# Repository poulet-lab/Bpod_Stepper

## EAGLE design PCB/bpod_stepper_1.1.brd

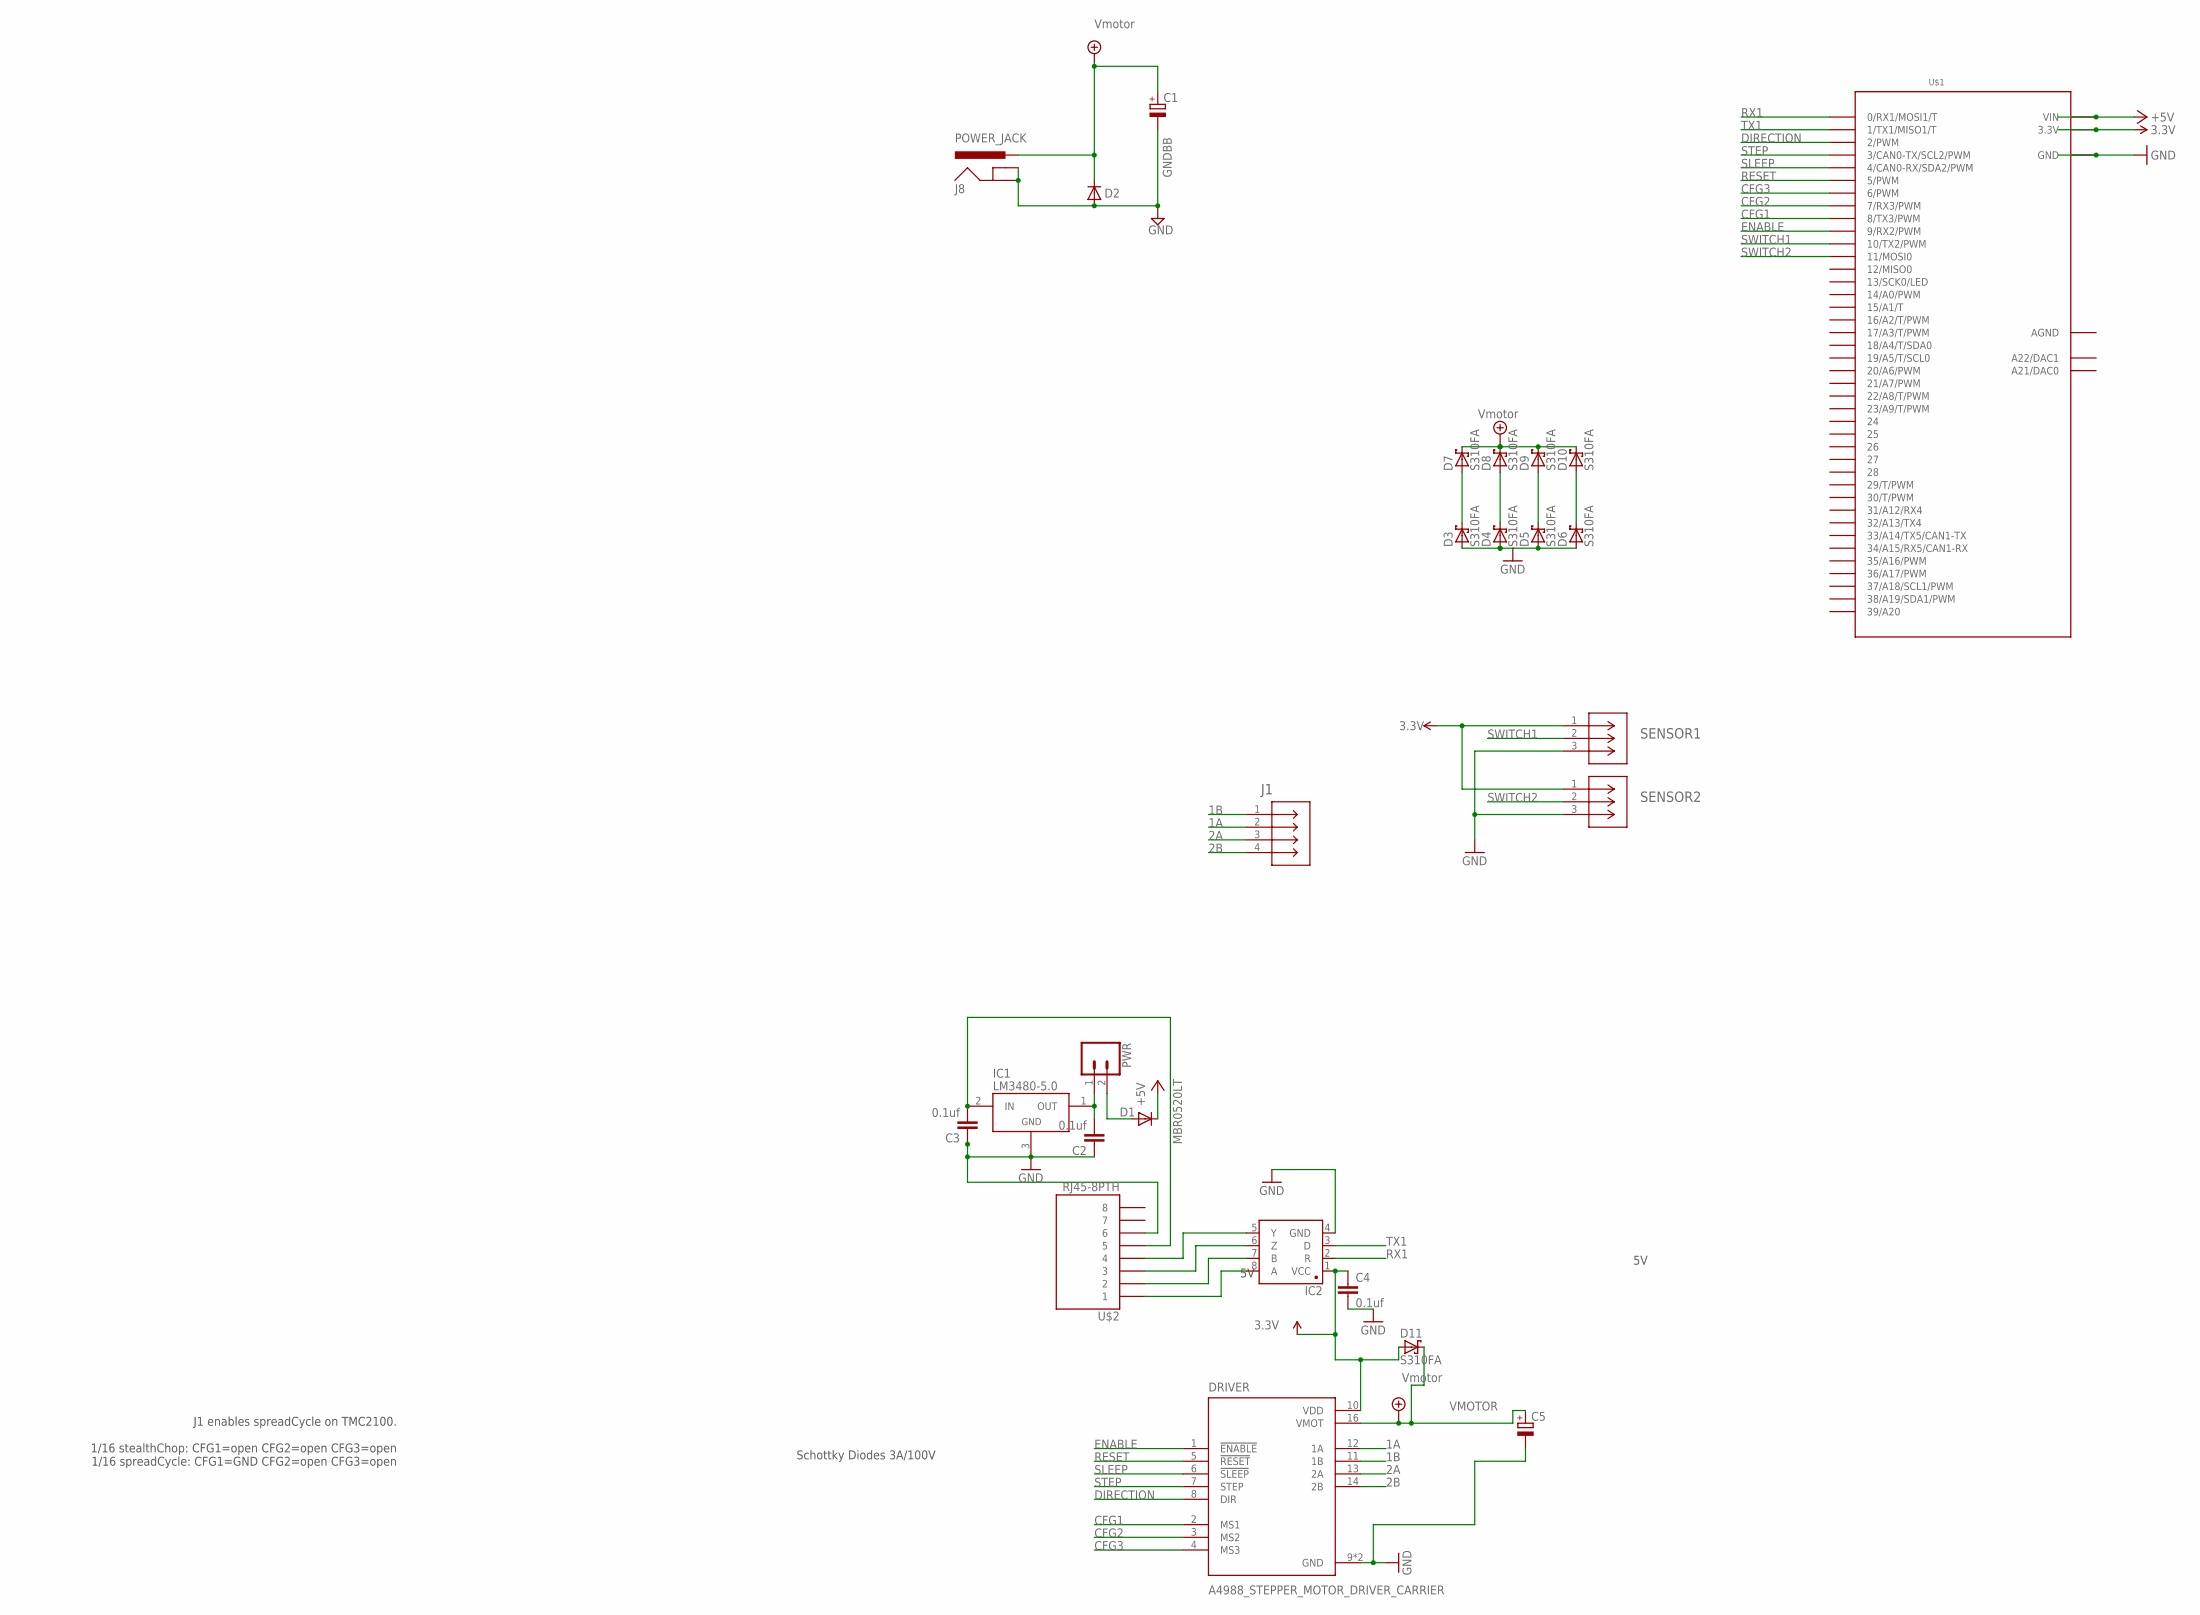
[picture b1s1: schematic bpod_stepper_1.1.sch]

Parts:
C1, C5: CPOL-EUG; PANASONIC_G
C2, C3, C4: 0.1uf; 1206@1
D1: MBR0520LT; SOD123
D2: DIODE-DO214AA; DO214AA
D3, D4, D5, D6, D7, D8, D9, D10, D11: S310FA; SOD123
DRIVER: A4988_STEPPER_MOTOR_DRIVER_CARRIER; MODULE_A4988_STEPPER_MOTOR_DRIVER_CARRIER
IC1: LM3480-5.0; SOT-23-3
IC2: SN65HVD31DR; SO08
J1: 282841-4; CONN4_282841-4_TEC
J8: POWER_JACK; POWER_JACK_PTH
PWR: CONN_02; 1X02
SENSOR1, SENSOR2: 282834-3; CONN_282834-3_TYC
U$1: TEENSY_3.6_DIL
U$2: RJ45-8PTH; RJ45-8

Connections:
1A: D4.C, D8.A, DRIVER.12 (1A), J1.2
1B: D3.C, D7.A, DRIVER.11 (1B), J1.1
2A: D5.C, D9.A, DRIVER.13 (2A), J1.3
2B: D6.C, D10.A, DRIVER.14 (2B), J1.4
3.3V: C4.1, D11.A, DRIVER.10 (VDD), IC2.1 (VCC), SENSOR1.1, SENSOR2.1, U$1.3.3V, U$1.3.3V3 (3.3V)
+5V: D1.C, U$1.VIN
AGND: U$1.AGND
CFG1: DRIVER.2 (MS1), U$1.8 (8/TX3/PWM)
CFG2: DRIVER.3 (MS2), U$1.7 (7/RX3/PWM)
CFG3: DRIVER.4 (MS3), U$1.6 (6/PWM)
DIRECTION: DRIVER.8 (DIR), U$1.2 (2/PWM)
ENABLE: DRIVER.1 (!ENABLE), U$1.9 (9/RX2/PWM)
GND: C1.-, C2.1, C3.1, C4.2, C5.-, D2.A, D3.A, D4.A, D5.A, D6.A, DRIVER.9 (GND), DRIVER.15 (GND), IC1.3 (GND), IC2.4 (GND), J8.GND, J8.GNDBREAK, SENSOR1.3, SENSOR2.3, U$1.GND, U$1.GND1 (GND), U$2.6
unnamed: IC2.8 (A), U$2.1
unnamed: IC2.7 (B), U$2.2
unnamed: IC2.6 (Z), U$2.3
unnamed: IC2.5 (Y), U$2.4
unnamed: C2.2, IC1.1 (OUT), PWR.1
unnamed: D1.A, PWR.2
unnamed: C3.2, IC1.2 (IN), U$2.5
RESET: DRIVER.5 (!RESET), U$1.5 (5/PWM)
RX1: IC2.2 (R), U$1.0 (0/RX1/MOSI1/T)
SLEEP: DRIVER.6 (!SLEEP), U$1.4 (4/CAN0-RX/SDA2/PWM)
STEP: DRIVER.7 (STEP), U$1.3 (3/CAN0-TX/SCL2/PWM)
SWITCH1: SENSOR1.2, U$1.10 (10/TX2/PWM)
SWITCH2: SENSOR2.2, U$1.11 (11/MOSI0)
TX1: IC2.3 (D), U$1.1 (1/TX1/MISO1/T)
VMOTOR: C1.+, C5.+, D2.C, D7.C, D8.C, D9.C, D10.C, D11.C, DRIVER.16 (VMOT), J8.PWR

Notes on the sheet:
GNDBB
Schottky Diodes 3A/100V
J1 enables spreadCycle on TMC2100. 1/16 stealthChop: CFG1=open CFG2=open CFG3=open 1/16 spreadCycle: CFG1=GND CFG2=open CFG3=open

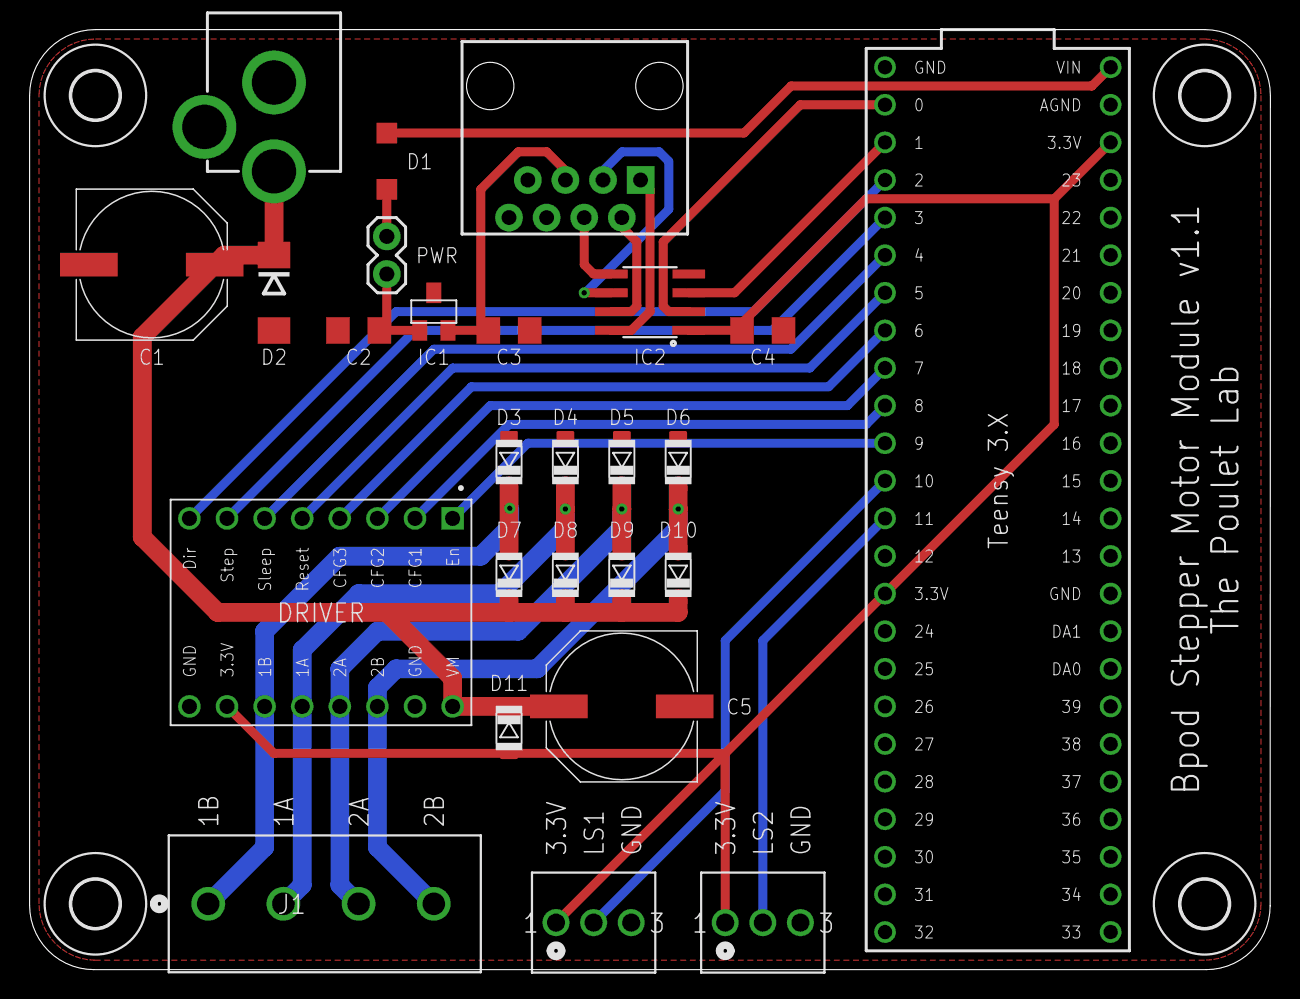
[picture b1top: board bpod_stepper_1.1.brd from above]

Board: 2 copper layers, 83.8 x 63.5 mm, 30 parts (0 on the bottom side), 27 nets.

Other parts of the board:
U$7, U$8, U$9, U$10: 3,2

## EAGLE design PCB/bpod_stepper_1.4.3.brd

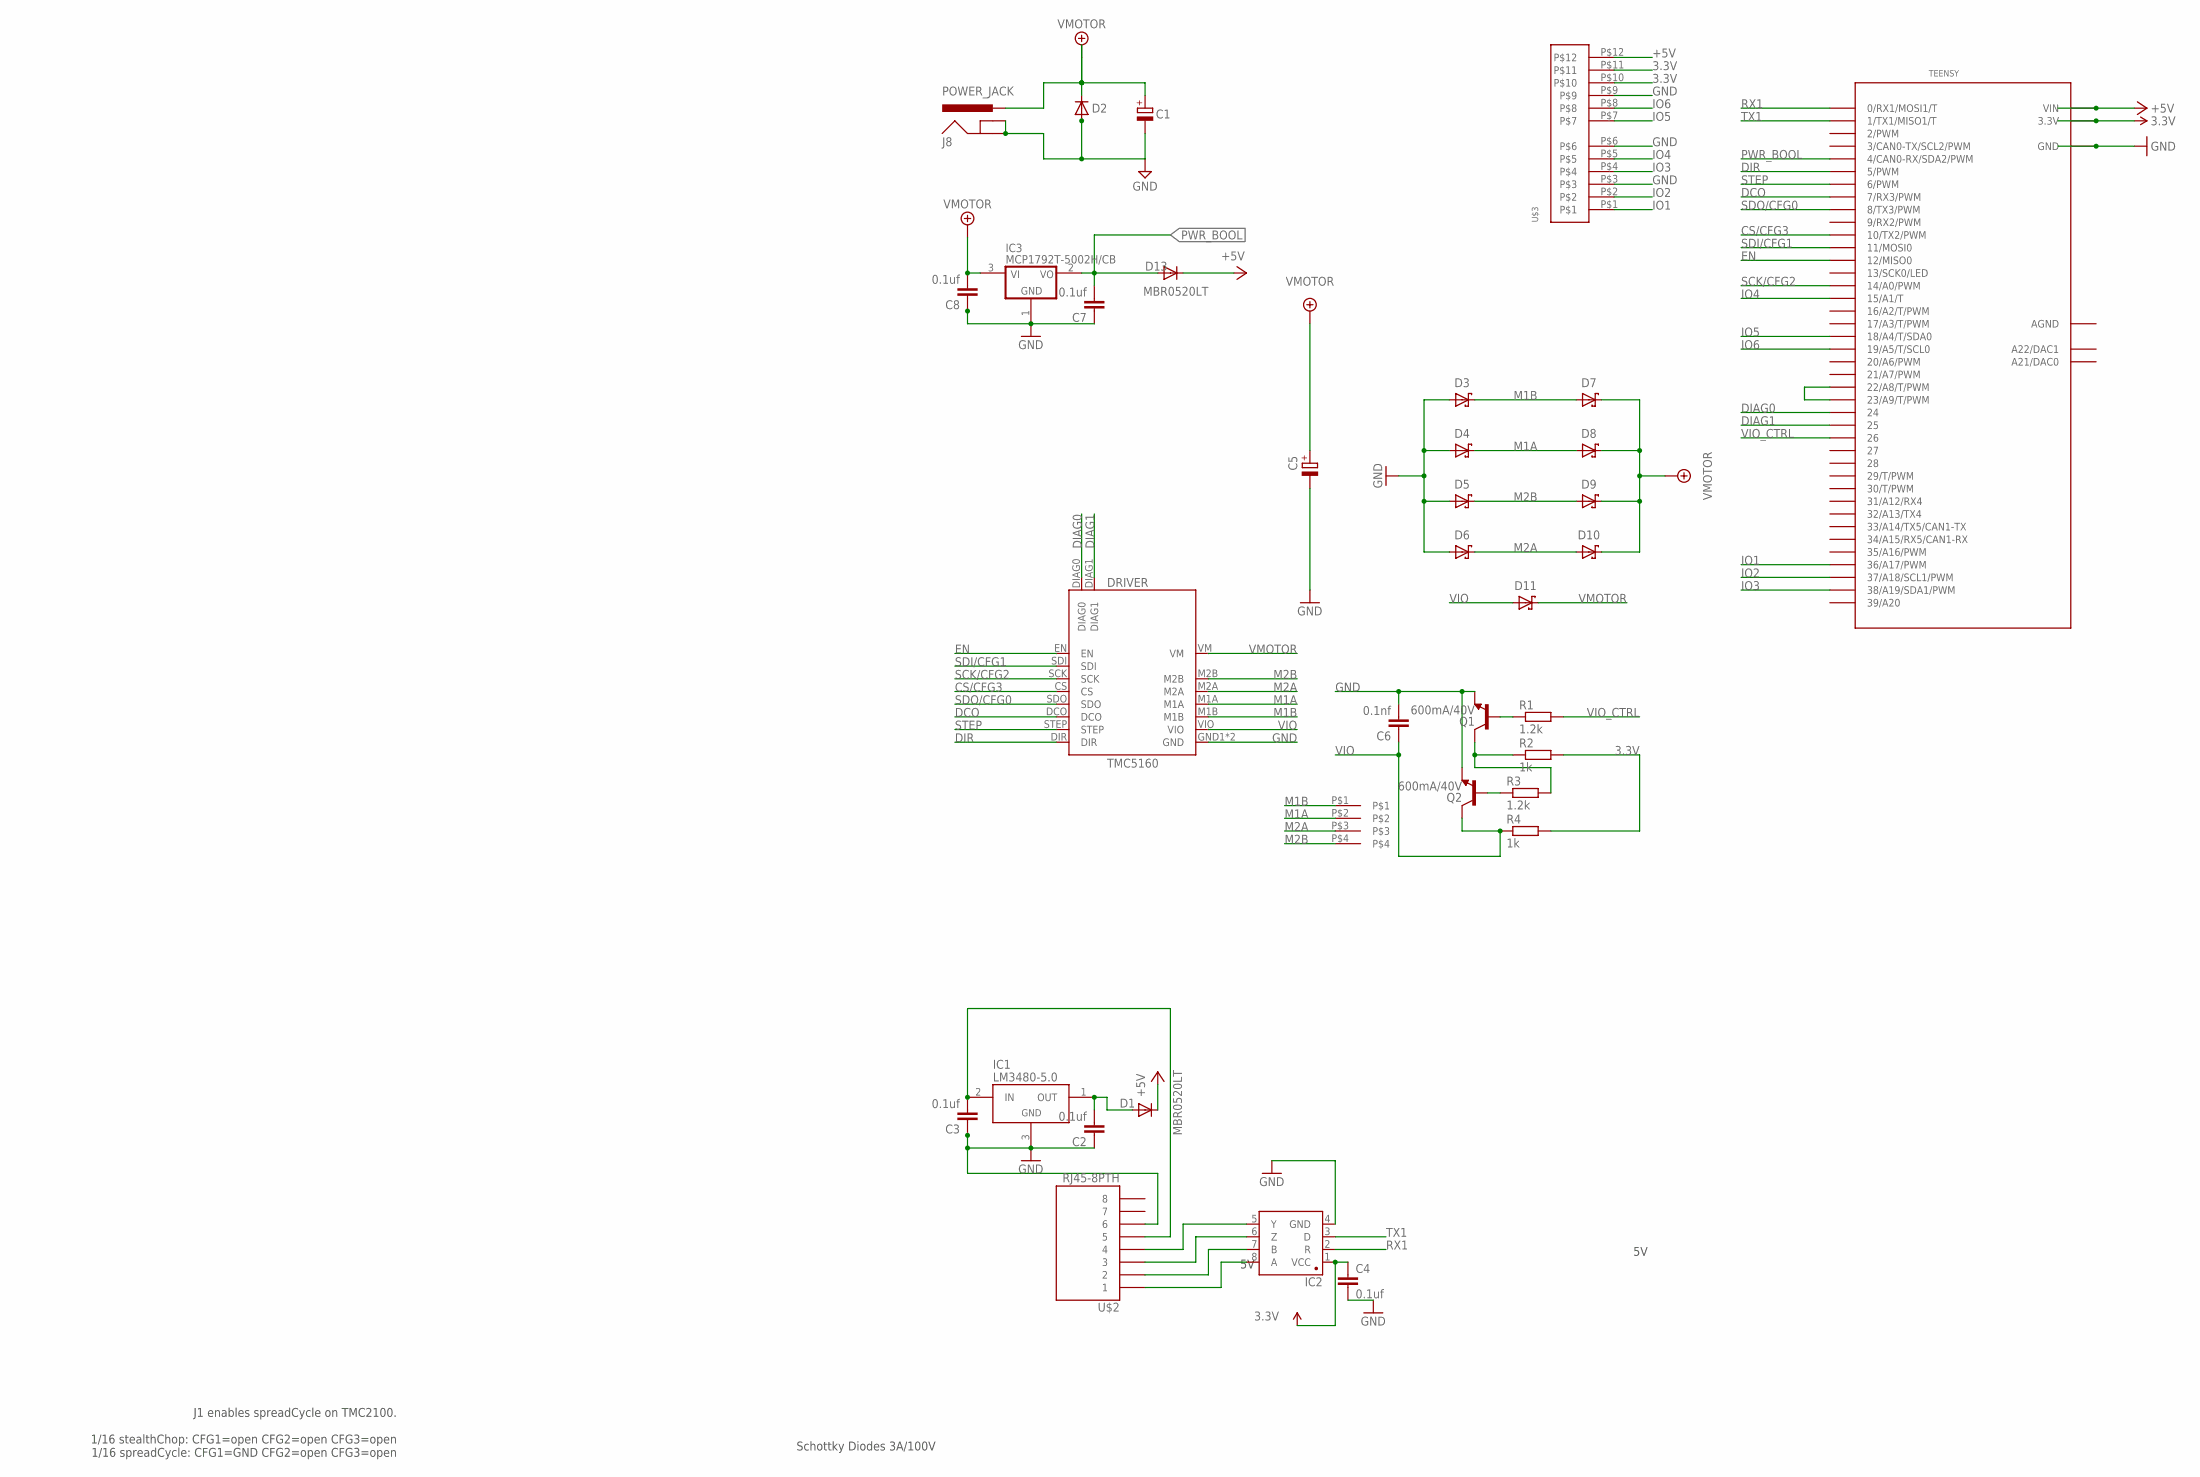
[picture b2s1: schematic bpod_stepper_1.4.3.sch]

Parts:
C1, C5: CPOL-EUG; PANASONIC_G
C2, C3, C4, C7, C8: 0.1uf; 1206@1
C6: 0.1nf; 1206@1
D1, D13: MBR0520LT; SOD123
D2: DIODE-DO214AA; DO214AA
D3, D4, D5, D6, D7, D8, D9, D10, D11: S310FA; SOD123
DRIVER: TMC5160
IC1: LM3480-5.0; SOT-23-3
IC2: SN65HVD31DR; SO08
IC3: MCP1792T-5002H/CB; SOT23A_MICROCHIP_CB
J8: POWER_JACK; POWER_JACK_PTH
Q1, Q2: 600mA/40V; SOT23-3
R1, R3: 1.2k; R1206
R2, R4: 1k; R1206
TEENSY: TEENSY_3.6_DIL
U$2: RJ45-8PTH; RJ45-8
U$3: 12POS_MOLEX_SOCKET
U$4: MOLEX395221004

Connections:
3.3V: C4.1, IC2.1 (VCC), R2.2, R4.2, TEENSY.3.3V, TEENSY.3.3V3 (3.3V), U$3.P$10, U$3.P$11
+5V: D1.C, D13.C, TEENSY.VIN, U$3.P$12
AGND: TEENSY.AGND
CS/CFG3: DRIVER.CS, TEENSY.10 (10/TX2/PWM)
DCO: DRIVER.DCO, TEENSY.7 (7/RX3/PWM)
DIAG0: DRIVER.DIAG0, TEENSY.24
DIAG1: DRIVER.DIAG1, TEENSY.25
DIR: DRIVER.DIR, TEENSY.5 (5/PWM)
EN: DRIVER.EN, TEENSY.12 (12/MISO0)
GND: C1.-, C2.1, C3.1, C4.2, C5.-, C6.2, C7.1, C8.1, D2.A, D3.A, D4.A, D5.A, D6.A, DRIVER.GND1 (GND), DRIVER.GND2 (GND), IC1.3 (GND), IC2.4 (GND), IC3.1 (GND), J8.GND, J8.GNDBREAK, Q1.2 (E), Q2.2 (E), TEENSY.GND, TEENSY.GND1 (GND), U$2.6, U$3.P$3, U$3.P$6, U$3.P$9
IO1: TEENSY.36/A17 (36/A17/PWM), U$3.P$1
IO2: TEENSY.37/A18 (37/A18/SCL1/PWM), U$3.P$2
IO3: TEENSY.38/A19 (38/A19/SDA1/PWM), U$3.P$4
IO4: TEENSY.15/A1 (15/A1/T), U$3.P$5
IO5: TEENSY.18/A4 (18/A4/T/SDA0), U$3.P$7
IO6: TEENSY.19/A5 (19/A5/T/SCL0), U$3.P$8
M1A: D4.C, D8.A, DRIVER.M1A, U$4.P$2
M1B: D3.C, D7.A, DRIVER.M1B, U$4.P$1
M2A: D6.C, D10.A, DRIVER.M2A, U$4.P$3
M2B: D5.C, D9.A, DRIVER.M2B, U$4.P$4
unnamed: TEENSY.22/A8 (22/A8/T/PWM), TEENSY.23/A9 (23/A9/T/PWM)
unnamed: Q1.3 (C), R2.1, R3.2
unnamed: Q2.1 (B), R3.1
unnamed: Q1.1 (B), R1.1
unnamed: IC2.8 (A), U$2.1
unnamed: IC2.7 (B), U$2.2
unnamed: IC2.6 (Z), U$2.3
unnamed: IC2.5 (Y), U$2.4
unnamed: C2.2, D1.A, IC1.1 (OUT)
unnamed: C3.2, IC1.2 (IN), U$2.5
PWR_BOOL: C7.2, D13.A, IC3.2 (VO), TEENSY.4 (4/CAN0-RX/SDA2/PWM)
RX1: IC2.2 (R), TEENSY.0 (0/RX1/MOSI1/T)
SCK/CFG2: DRIVER.SCK, TEENSY.14/A0 (14/A0/PWM)
SDI/CFG1: DRIVER.SDI, TEENSY.11 (11/MOSI0)
SDO/CFG0: DRIVER.SDO, TEENSY.8 (8/TX3/PWM)
STEP: DRIVER.STEP, TEENSY.6 (6/PWM)
TX1: IC2.3 (D), TEENSY.1 (1/TX1/MISO1/T)
VIO: C6.1, D11.A, DRIVER.VIO, Q2.3 (C), R4.1
VIO_CTRL: R1.2, TEENSY.26
VMOTOR: C1.+, C5.+, C8.2, D2.C, D7.C, D8.C, D9.C, D10.C, D11.C, DRIVER.VM, IC3.3 (VI), J8.PWR

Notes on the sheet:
Schottky Diodes 3A/100V
J1 enables spreadCycle on TMC2100. 1/16 stealthChop: CFG1=open CFG2=open CFG3=open 1/16 spreadCycle: CFG1=GND CFG2=open CFG3=open

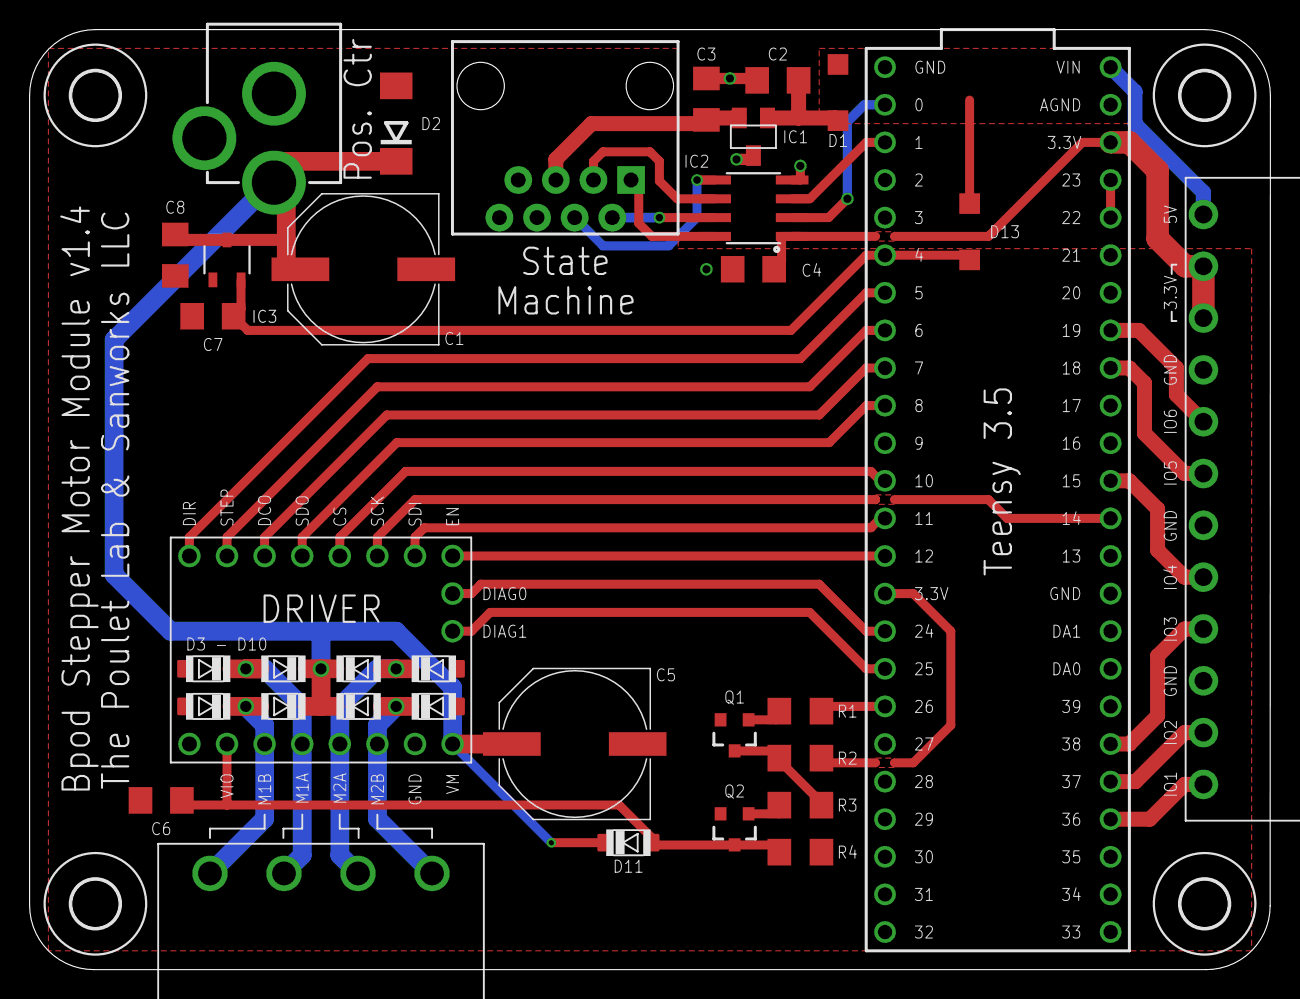
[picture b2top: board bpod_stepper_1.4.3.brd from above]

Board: 2 copper layers, 83.8 x 63.5 mm, 39 parts (0 on the bottom side), 39 nets.

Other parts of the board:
U$7, U$8, U$9, U$10: 3,2

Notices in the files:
parts and their libraries:
SparkFun-Capacitors: Licensing: Creative Commons ShareAlike 4.0 International - https://creativecommons.org/licenses/by-sa/4.0
SparkFun: Licensing: CC v3.0 Share-Alike You are welcome to use this library for commercial purposes.
COPYRIGHT: Copyright (C) 2016 Accelerated Designs. All rights reserved
